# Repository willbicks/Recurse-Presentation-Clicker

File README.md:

# USB Presentation Clicker - PCB and firmware

## The Recurse Center - 15 Minute Non-Programming Talk

This project was created as a 15 minute intro to circuit board concepts and design, including a live demonstration of the process of schematic capture and PCB design for this simple presentation clicker.

[The slides for the talk leading up to the demo are available here.](https://docs.google.com/presentation/d/1ne3fzInx9VCI7aZ8SwKrGWYj8iwI68Q8ZW5xORLohZw)

## Printed Circuit Board

The schematic and board design are made with KiCAD 9.0, available from [kicad.org](https://www.kicad.org/). The project file is at [`rc-demo.kicad_pro`](./rc-demo.kicad_pro).

The schematic and board layours were done live in front of an audience in around 10 minutes, so there's lots of room for improvement or expansion. Try tweaking the design to fit your sensibilities, or deleting the current design and starting fresh!

To learn more about KiCAD, check out their [getting started guide](https://docs.kicad.org/9.0/en/getting_started_in_kicad/getting_started_in_kicad.html#basic_concepts_and_workflow).

## Firmware

The firmware for the remote is written in Rust, using the `rp_pico` board support package and `embedded-hal` traits, and using the [`usbd_human_interface_device`](https://crates.io/crates/usbd-human-interface-device) crate to implement the USB HID protocol for a keyboard. The firmware entrypoint is at [`src/main.rs`](./src/main.rs).

If you've installed the rust toolchain with `rustup`, the appropriate extras will be installed automatically as defined in the [`rust-toolchain.toml`](./rust-toolchain.toml) file. The only additional requirement is to install one (or both) of the following tools for flashing the firmware to the RP2040:

```shell
# Install probe-rs for flashing and debugging with debugging probe (requires cargo-binstall)
cargo binstall probe-rs-tools
# Install elf2uf2-rs to flash via RP2040 USB bootloader
cargo install elf2uf2-rs
```

By default, `cargo run` will use probe-rs to load and debug the firmware:

```shell
cargo run
```

To flash the firmware via the RP2040 USB bootloader, you can use:

```shell
cargo build
elf2uf2-rs ./target/thumbv6m-none-eabi/debug/usb-presentation-remote
```

And then copy the `./target/thumbv6m-none-eabi/debug/usb-presentation-remote.uf2` to the `RPI-RP2` drive that appears when you hold the BOOTSEL button on the RP2040 board while plugging it into your computer.

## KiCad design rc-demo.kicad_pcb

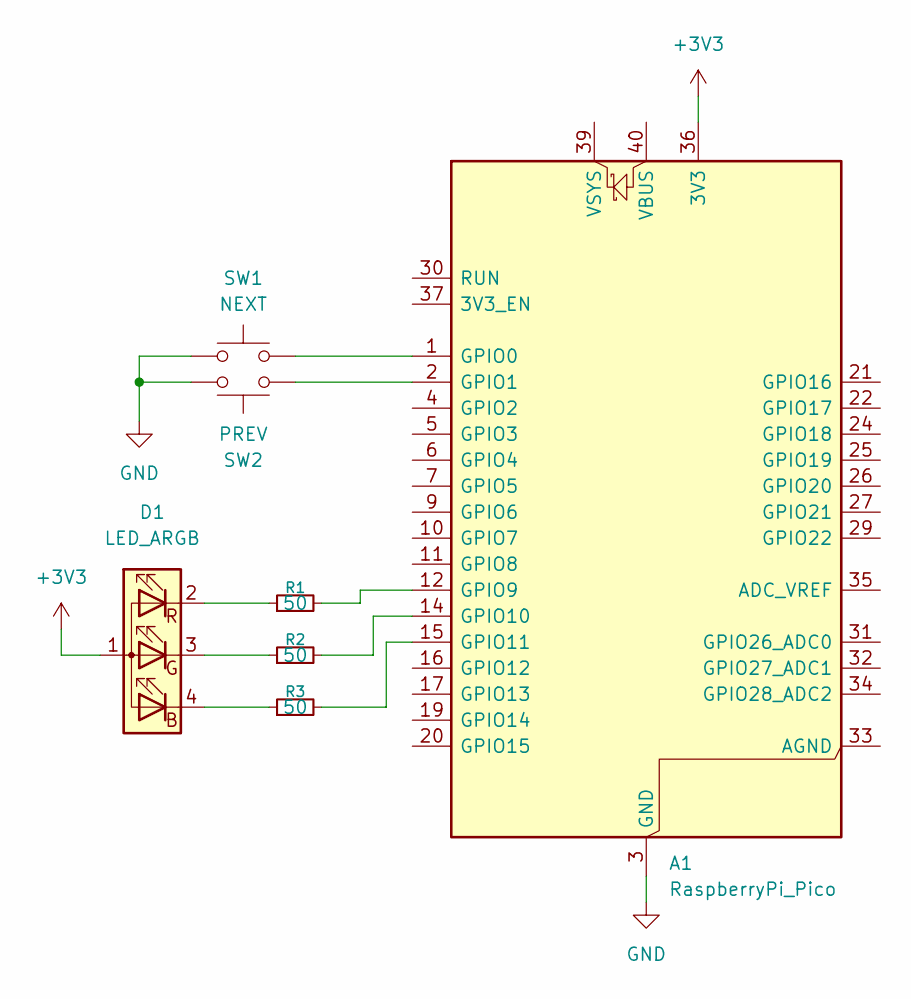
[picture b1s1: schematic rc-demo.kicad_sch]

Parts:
A1: RaspberryPi_Pico; RaspberryPi_Pico_Common_Unspecified
D1: LED_ARGB; LED_D5.0mm-4_RGB_Wide_Pins
R1, R2, R3: 50; R_Axial_DIN0204_L3.6mm_D1.6mm_P5.08mm_Horizontal
SW1: NEXT; SW_Cherry_MX_1.00u_PCB
SW2: PREV; SW_Cherry_MX_1.00u_PCB

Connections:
+3V3: A1.36 (3V3), D1.1 (A)
GND: A1.3 (GND), A1.8 (GND), A1.13 (GND), A1.18 (GND), A1.23 (GND), A1.28 (GND), A1.38 (GND), SW1.1, SW2.1
unnamed: A1.1 (GPIO0), SW1.2
unnamed: A1.2 (GPIO1), SW2.2
unnamed: A1.12 (GPIO9), R1.2
unnamed: A1.14 (GPIO10), R2.2
unnamed: A1.15 (GPIO11), R3.2
unnamed: D1.4 (BK), R3.1
unnamed: D1.3 (GK), R2.1
unnamed: D1.2 (RK), R1.1

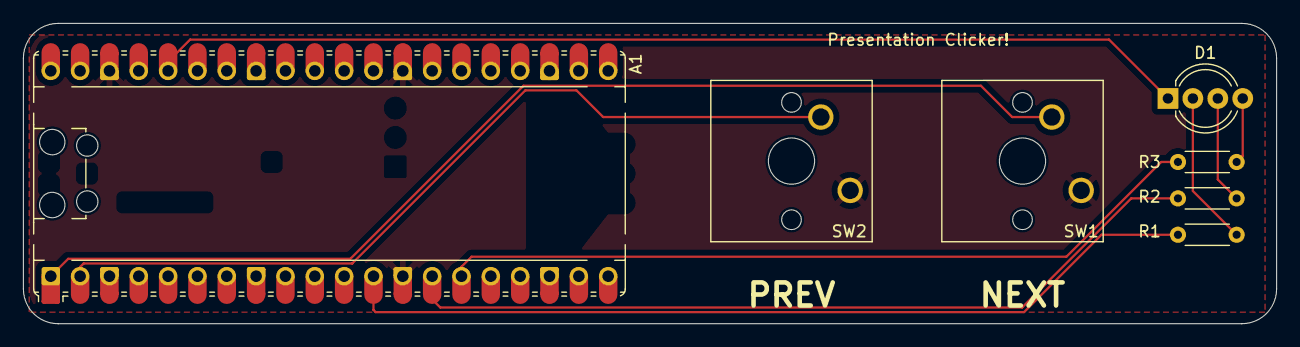
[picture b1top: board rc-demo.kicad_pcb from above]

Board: 2 copper layers, 108.5 x 26.0 mm, 7 parts (0 on the bottom side), 10 nets.

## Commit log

2025-06-05 Add clicker KiCAD project.
2025-06-05 Add Rust firmware source.
2025-06-05 Add README.
